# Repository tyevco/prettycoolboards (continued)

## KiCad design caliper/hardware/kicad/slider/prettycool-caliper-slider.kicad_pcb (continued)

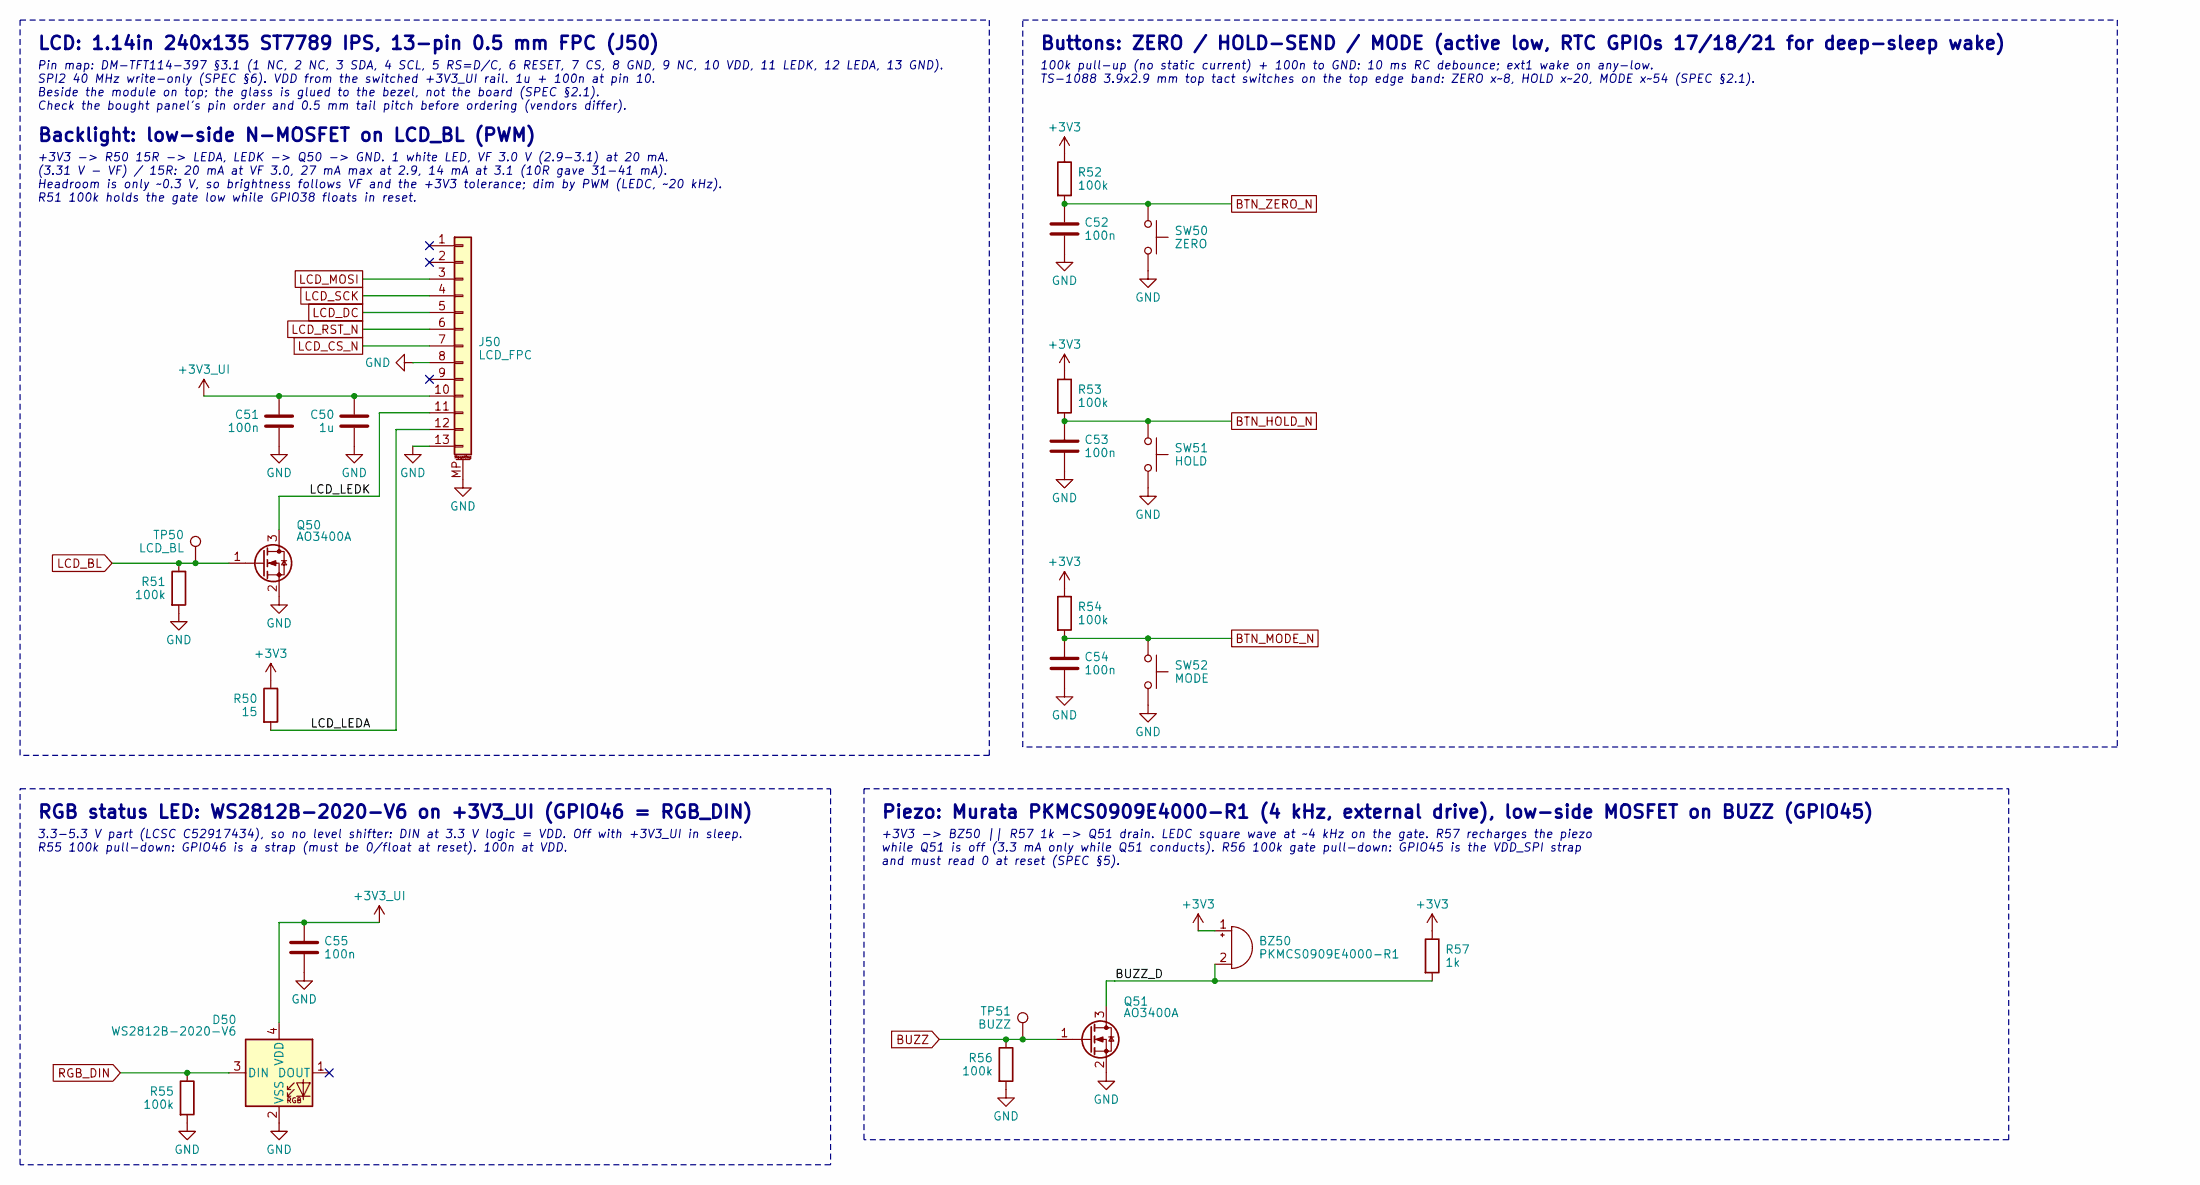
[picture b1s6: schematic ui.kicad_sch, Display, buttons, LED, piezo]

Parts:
BZ50: PKMCS0909E4000-R1; Buzzer_Murata_PKMCS0909E; MPN PKMCS0909E4000-R1; LCSC C910763
C50: 1u; C_0402_1005Metric; MPN CL05A105KA5NQNC; LCSC C52923
C51, C52, C53, C54, C55: 100n; C_0402_1005Metric; MPN CL05B104KO5NNNC; LCSC C1525
D50: WS2812B-2020-V6; LED_WS2812B-2020_PLCC4_2.0x2.0mm; MPN WS2812B-2020-V6; LCSC C52917434
J50: LCD_FPC; HDGC_0.5K-AX-13PWB_1x13-1MP_P0.50mm_Horizontal; MPN 0.5K-AX-13PWB; LCSC C2911931
Q50, Q51: AO3400A; SOT-23; MPN AO3400A; LCSC C20917
R50: 15; R_0603_1608Metric; MPN 0603WAF150JT5E; LCSC C22810
R51, R52, R53, R54, R55, R56: 100k; R_0402_1005Metric; MPN 0402WGF1003TCE; LCSC C25741
R57: 1k; R_0402_1005Metric; MPN 0402WGF1001TCE; LCSC C11702
SW50: ZERO; SW_SPST_TS-1088-xR020; MPN TS-1088-AR02016; LCSC C720477
SW51: HOLD; SW_SPST_TS-1088-xR020; MPN TS-1088-AR02016; LCSC C720477
SW52: MODE; SW_SPST_TS-1088-xR020; MPN TS-1088-AR02016; LCSC C720477
TP50: LCD_BL; TestPoint_Pad_D1.0mm
TP51: BUZZ; TestPoint_Pad_D1.0mm

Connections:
+3V3: BZ50.1 (+), R50.1, R52.1, R53.1, R54.1, R57.1; also elsewhere on the board
+3V3_UI: C50.1, C51.1, C55.1, D50.4 (VDD), J50.10; also elsewhere on the board
/Display, buttons, LED, piezo/BUZZ_D: BZ50.2 (-), Q51.3 (D), R57.2
/Display, buttons, LED, piezo/LCD_LEDA: J50.12, R50.2
/Display, buttons, LED, piezo/LCD_LEDK: J50.11, Q50.3 (D)
BTN_HOLD_N: C53.1, R53.2, SW51.1; also elsewhere on the board
BTN_MODE_N: C54.1, R54.2, SW52.1; also elsewhere on the board
BTN_ZERO_N: C52.1, R52.2, SW50.1; also elsewhere on the board
BUZZ: Q51.1 (G), R56.1, TP51.1; also elsewhere on the board
GND: C50.2, C51.2, C52.2, C53.2, C54.2, C55.2, D50.2 (VSS), J50.8, J50.13, J50.MP (MountPin), Q50.2 (S), Q51.2 (S), R51.2, R55.2, R56.2, SW50.2, SW51.2, SW52.2; also elsewhere on the board
LCD_BL: Q50.1 (G), R51.1, TP50.1; also elsewhere on the board
LCD_CS_N: J50.7; also elsewhere on the board
LCD_DC: J50.5; also elsewhere on the board
LCD_MOSI: J50.3; also elsewhere on the board
LCD_RST_N: J50.6; also elsewhere on the board
LCD_SCK: J50.4; also elsewhere on the board
RGB_DIN: D50.3 (DIN), R55.1; also elsewhere on the board

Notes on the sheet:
LCD: 1.14in 240x135 ST7789 IPS, 13-pin 0.5 mm FPC (J50)
Pin map: DM-TFT114-397 §3.1 (1 NC, 2 NC, 3 SDA, 4 SCL, 5 RS=D/C, 6 RESET, 7 CS, 8 GND, 9 NC, 10 VDD, 11 LEDK, 12 LEDA, 13 GND). SPI2 40 MHz write-only (SPEC §6). VDD from the switched +3V3_UI rail. 1u + 100n at pin 10. Beside the module on top; the glass is glued to the bezel, not the board (SPEC §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
Backlight: low-side N-MOSFET on LCD_BL (PWM)
+3V3 -> R50 15R -> LEDA, LEDK -> Q50 -> GND. 1 white LED, VF 3.0 V (2.9-3.1) at 20 mA. (3.31 V - VF) / 15R: 20 mA at VF 3.0, 27 mA max at 2.9, 14 mA at 3.1 (10R gave 31-41 mA). Headroom is only ~0.3 V, so brightness follows VF and the +3V3 tolerance; dim by PWM (LEDC, ~20 kHz). R51 100k holds the g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
Buttons: ZERO / HOLD-SEND / MODE (active low, RTC GPIOs 17/18/21 for deep-sleep wake)
100k pull-up (no static current) + 100n to GND: 10 ms RC debounce; ext1 wake on any-low. TS-1088 3.9x2.9 mm top tact switches on the top edge band: ZERO x~8, HOLD x~20, MODE x~54 (SPEC §2.1).
RGB status LED: WS2812B-2020-V6 on +3V3_UI (GPIO46 = RGB_DIN)
3.3-5.3 V part (LCSC C52917434), so no level shifter: DIN at 3.3 V logic = VDD. Off with +3V3_UI in sleep. R55 100k pull-down: GPIO46 is a strap (must be 0/float at reset). 100n at VDD.
Piezo: Murata PKMCS0909E4000-R1 (4 kHz, external drive), low-side MOSFET on BUZZ (GPIO45)
+3V3 -> BZ50 || R57 1k -> Q51 drain. LEDC square wave at ~4 kHz on the gate. R57 recharges the piezo while Q51 is off (3.3 mA only while Q51 conducts). R56 100k gate pull-down: GPIO45 is the VDD_SPI strap and must read 0 at reset (SPEC §5).

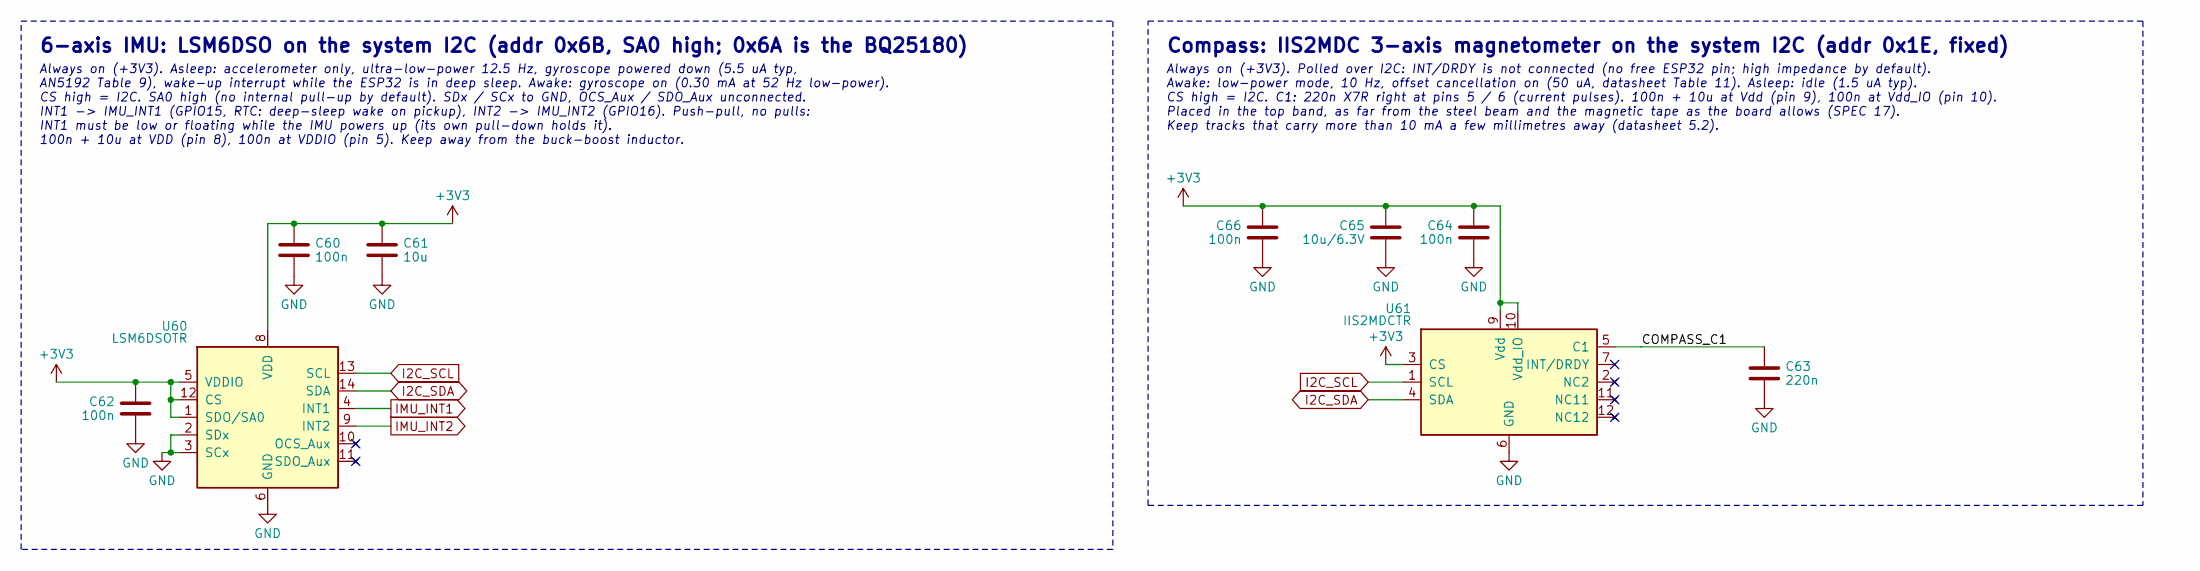
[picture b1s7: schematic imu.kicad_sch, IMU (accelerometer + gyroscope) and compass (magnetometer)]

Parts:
C60, C62, C64, C66: 100n; C_0402_1005Metric; MPN CL05B104KO5NNNC; LCSC C1525
C61: 10u; C_0603_1608Metric; MPN CL10A106KP8NNNC; LCSC C19702
C63: 220n; C_0402_1005Metric; MPN CL05B224KO5NNNC; LCSC C16772
C65: 10u/6.3V; C_0402_1005Metric; MPN CL05A106MQ5NUNC; LCSC C15525
U60: LSM6DSOTR; LGA-14_3x2.5mm_P0.5mm_LayoutBorder3x4y; MPN LSM6DSOTR; LCSC C2655100
U61: IIS2MDCTR; LGA-12_2x2mm_P0.5mm; MPN IIS2MDCTR; LCSC C2655002

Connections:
+3V3: C60.2, C61.2, C62.2, C64.2, C65.2, C66.2, U60.1 (SDO/SA0), U60.5 (VDDIO), U60.8 (VDD), U60.12 (CS), U61.3 (CS), U61.9 (Vdd), U61.10 (Vdd_IO); also elsewhere on the board
/IMU (accelerometer + gyroscope) and compass (magnetometer)/COMPASS_C1: C63.1, U61.5 (C1)
GND: C60.1, C61.1, C62.1, C63.2, C64.1, C65.1, C66.1, U60.2 (SDx), U60.3 (SCx), U60.6 (GND), U60.7 (GND), U61.6 (GND), U61.8 (GND); also elsewhere on the board
I2C_SCL: U60.13 (SCL), U61.1 (SCL); also elsewhere on the board
I2C_SDA: U60.14 (SDA), U61.4 (SDA); also elsewhere on the board
IMU_INT1: U60.4 (INT1); also elsewhere on the board
IMU_INT2: U60.9 (INT2); also elsewhere on the board

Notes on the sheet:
6-axis IMU: LSM6DSO on the system I2C (addr 0x6B, SA0 high; 0x6A is the BQ25180)
Always on (+3V3). Asleep: accelerometer only, ultra-low-power 12.5 Hz, gyroscope powered down (5.5 uA typ, AN5192 Table 9), wake-up interrupt while the ESP32 is in deep sleep. Awake: gyroscope on (0.30 mA at 52 Hz low-power). CS high = I2C. SA0 high (no internal pull-up by default). SDx / SCx to GN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
Compass: IIS2MDC 3-axis magnetometer on the system I2C (addr 0x1E, fixed)
Always on (+3V3). Polled over I2C: INT/DRDY is not connected (no free ESP32 pin; high impedance by default). Awake: low-power mode, 10 Hz, offset cancellation on (50 uA, datasheet Table 11). Asleep: idle (1.5 uA typ). CS high = I2C. C1: 220n X7R right at pins 5 / 6 (current pulses). 100n + 10u at V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

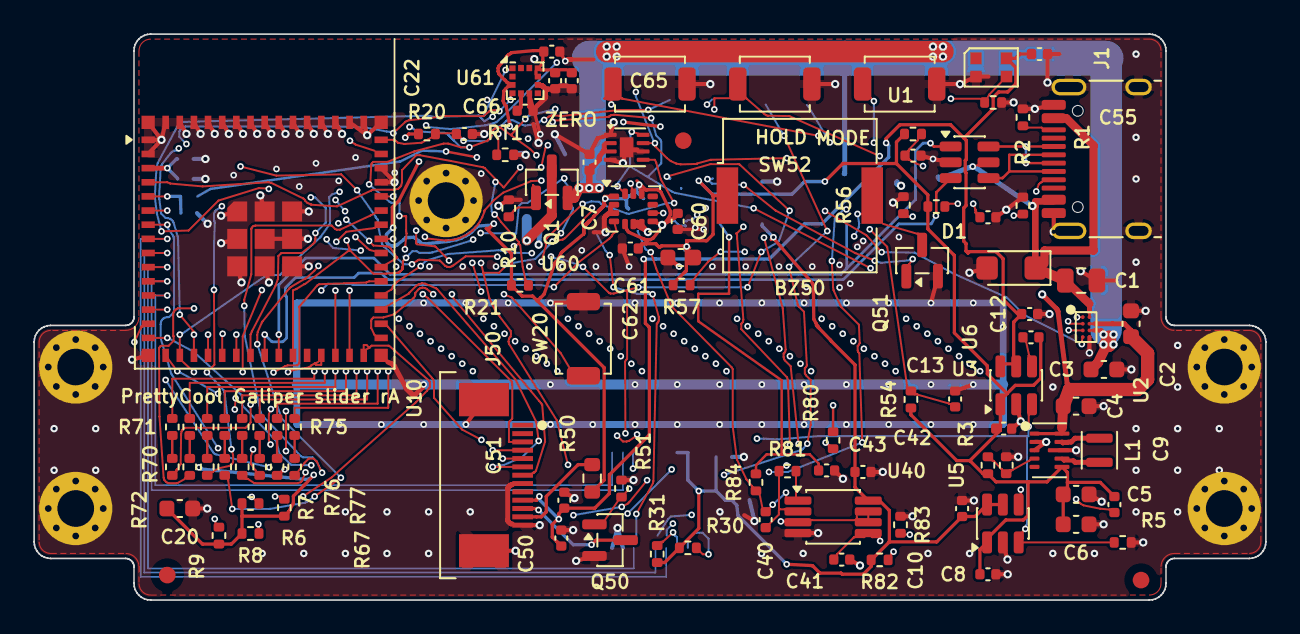
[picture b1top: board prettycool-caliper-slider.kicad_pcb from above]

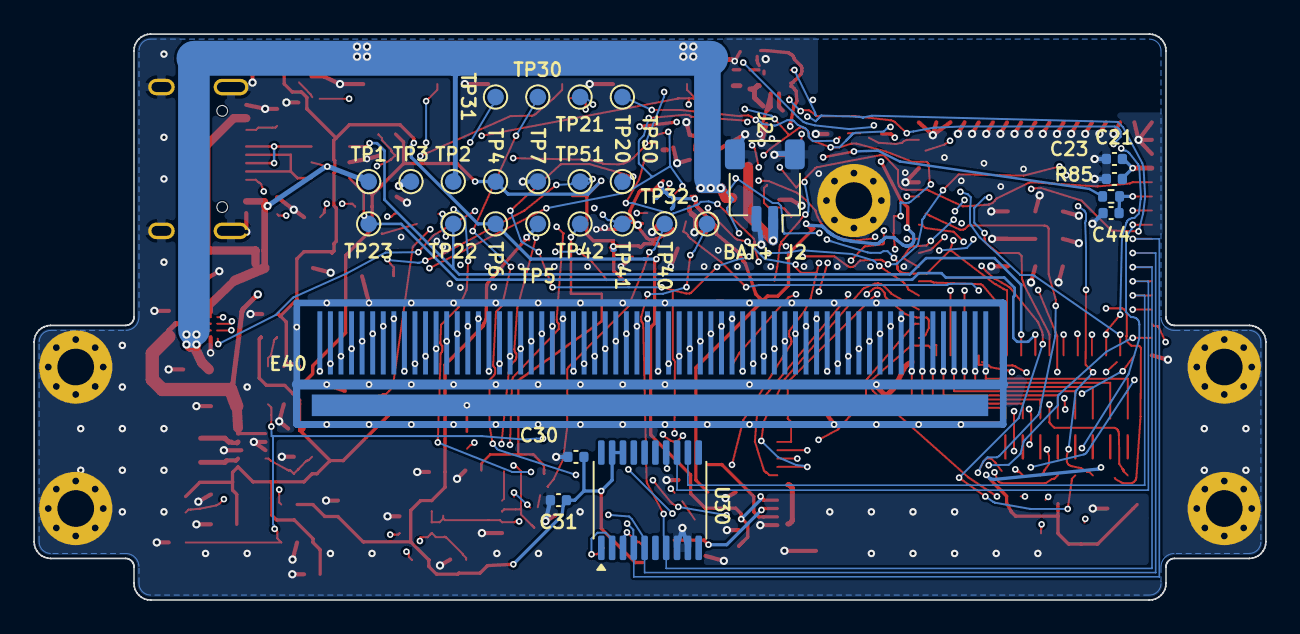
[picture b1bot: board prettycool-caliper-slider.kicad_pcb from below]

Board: 4 copper layers, 74.0 x 34.0 mm, 135 parts (28 on the bottom side), 82 nets.

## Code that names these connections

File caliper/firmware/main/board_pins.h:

/*
 * GENERATED by firmware/tools/gen_pins.py from caliper/hardware/design/nets.py. Do not edit.
 * nets.py REV A 2026-11-07
 */
#pragma once

#define BOARD_PINS_HASH "202d301f8ed3b0f1"
#define BOARD_REV "A"

/* GPIO number per net (ESP32-S3-MINI-1) */
#define PIN_BOOT_N      0  /* BOOT_N */
#define PIN_CAP_RX      1  /* CAP_RX */
#define PIN_FG_ALRT_N   2  /* FG_ALRT_N */
#define PIN_CHG_INT_N   3  /* CHG_INT_N */
#define PIN_MAG_A       4  /* MAG_A */
#define PIN_MAG_B       5  /* MAG_B */
#define PIN_MAG_IDX     6  /* MAG_IDX */
#define PIN_MAG_CLK     7  /* MAG_CLK */
#define PIN_MAG_DO      8  /* MAG_DO */
#define PIN_MAG_CSN     9  /* MAG_CSN */
#define PIN_MAG_INC_N  10  /* MAG_INC_N */
#define PIN_MAG_DEC_N  11  /* MAG_DEC_N */
#define PIN_SNS_PWR_EN 12  /* SNS_PWR_EN */
#define PIN_I2C_SDA    13  /* I2C_SDA */
#define PIN_I2C_SCL    14  /* I2C_SCL */
#define PIN_IMU_INT1   15  /* IMU_INT1 */
#define PIN_IMU_INT2   16  /* IMU_INT2 */
#define PIN_BTN_ZERO_N 17  /* BTN_ZERO_N */
#define PIN_BTN_HOLD_N 18  /* BTN_HOLD_N */
#define PIN_USB_DM     19  /* USB_DM */
#define PIN_USB_DP     20  /* USB_DP */
#define PIN_BTN_MODE_N 21  /* BTN_MODE_N */
#define PIN_LCD_SCK    33  /* LCD_SCK */
#define PIN_LCD_MOSI   34  /* LCD_MOSI */
#define PIN_LCD_CS_N   35  /* LCD_CS_N */
#define PIN_LCD_DC     36  /* LCD_DC */
#define PIN_LCD_RST_N  37  /* LCD_RST_N */
#define PIN_LCD_BL     38  /* LCD_BL */
#define PIN_CAP_TX0    39  /* CAP_TX0 */
#define PIN_CAP_TX1    40  /* CAP_TX1 */
#define PIN_CAP_TX2    41  /* CAP_TX2 */
#define PIN_CAP_TX3    42  /* CAP_TX3 */
#define PIN_CAP_TX6    43  /* CAP_TX6 */
#define PIN_CAP_TX7    44  /* CAP_TX7 */
#define PIN_BUZZ       45  /* BUZZ */
#define PIN_RGB_DIN    46  /* RGB_DIN */
#define PIN_CAP_TX4    47  /* CAP_TX4 */
#define PIN_CAP_TX5    48  /* CAP_TX5 */

/* 7-bit I2C addresses */
#define I2C_ADDR_BQ25180    0x6A
#define I2C_ADDR_IIS2MDC    0x1E
#define I2C_ADDR_LSM6DSO    0x6B
#define I2C_ADDR_MAX17048   0x36

/* CAP_TX0..7 in phase order, for the dedicated-GPIO bundle */
#define PIN_CAP_TX_LIST { PIN_CAP_TX0, PIN_CAP_TX1, PIN_CAP_TX2, PIN_CAP_TX3, PIN_CAP_TX4, PIN_CAP_TX5, PIN_CAP_TX6, PIN_CAP_TX7 }

/* every GPIO above, for checks (test/host/test_pin_plan.c: each one is in the pin plan) */
#define BOARD_PINS_COUNT 38
#define BOARD_PINS_ALL { \
    PIN_BOOT_N, PIN_CAP_RX, PIN_FG_ALRT_N, PIN_CHG_INT_N, PIN_MAG_A, PIN_MAG_B, \
    PIN_MAG_IDX, PIN_MAG_CLK, PIN_MAG_DO, PIN_MAG_CSN, PIN_MAG_INC_N, PIN_MAG_DEC_N, \
    PIN_SNS_PWR_EN, PIN_I2C_SDA, PIN_I2C_SCL, PIN_IMU_INT1, PIN_IMU_INT2, PIN_BTN_ZERO_N, \
    PIN_BTN_HOLD_N, PIN_USB_DM, PIN_USB_DP, PIN_BTN_MODE_N, PIN_LCD_SCK, PIN_LCD_MOSI, \
    PIN_LCD_CS_N, PIN_LCD_DC, PIN_LCD_RST_N, PIN_LCD_BL, PIN_CAP_TX0, PIN_CAP_TX1, \
    PIN_CAP_TX2, PIN_CAP_TX3, PIN_CAP_TX6, PIN_CAP_TX7, PIN_BUZZ, PIN_RGB_DIN, \
    PIN_CAP_TX4, PIN_CAP_TX5 \
}

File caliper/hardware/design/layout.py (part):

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        "D50": (51.5, 32.0, 0.0, "F"),
        # 2026-11-09 slim housing (owner decision): J2 on the BOTTOM, hanging into the battery pocket's J2 bay (board
        # x 21.5..27.6, y 22.4..35.1), mating face toward +y (the top edge), signal pads toward -y (pad row y 22.9,
        # pin 1 VBAT_RAW at x 23.6). Body x 22.1..26.1, y 23.2..27.5, 2.95 below the board; the mated plug x 21.9..26.3,
        # y 27.5..32.1. Was (24.5, 30.6) rot 180 on top, mouth over the top edge (plug relief past y 34 in the housing).
        # >= 6.3 mm in plan from the antenna area, >= 0.9 mm from H1's boss
        "J2": (24.1, 24.9, 0.0, "B"),
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        # (2.0, 25.95): C21 100n above, C23 10u below, +3V3 pad (1) toward the via. 0402, 0.5 mm tall, in the upper
        # band where the housing floor is 0.75 mm below the board (SPEC §2.1); clear of the antenna rule area (y >= 29.2)
        "C21": (3.1, 26.5, 0.0, "B"), "C23": (3.1, 25.3, 0.0, "B"),
        # CAP_RX anti-alias RC (3.9k / 100p) at the ADC pin (review 2026-11-08: it sat at U40, 40 mm of track from
        # GPIO1): bottom, under the module, below C23, beside GPIO1's escape via (2.0, 24.25); R85 pad 2 (CAP_RX)
        # and C44 pad 1 (CAP_RX) face the via. 0.2 mm from every other net (the Analog class), 0.5 mm tall
        "R85": (3.3, 24.25, 180.0, "B"), "C44": (3.3, 23.25, 0.0, "B"),
        # FID3 (SPEC 60.5, 32.8) would sit inside J1's courtyard (it reaches y 31.9 over x 54-63): top middle instead
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        if ref in fps:
            d = local_dir_board(fps[ref], lx, ly)
            assert abs(d[0] - want[0]) < 0.05 and abs(d[1] - want[1]) < 0.05, f"{ref} opens toward {d}, want {want}"
    if "J2" in fps:      # bottom side; a bottom part is mirrored, so pin 1 (VBAT_RAW) is the -x one of the pair
        assert fps["J2"].IsFlipped(), "J2 must be on the bottom (SPEC §2.1)"
        p1, p2 = pad_xy(fps["J2"], "1"), pad_xy(fps["J2"], "2")
        assert abs(p1[1] - 22.9) < 0.01 and p1[0] < p2[0], f"J2 pins at {p1} / {p2}, want the row at y 22.9, pin 1 -x"
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                   # the module peaks at ~0.36 A) in a class the grid router may rip up and re-route
                   rail_nets=("+3V3",),
                   light_power=("+3V3_SNS", "+3V3_UI", "LCD_LEDA", "LCD_LEDK"),
                   # CAP_RX (GPIO1, ADC) and the long run to its filter's first stage (review 2026-11-08)
                   analog_nets=("CAP_RX", "CAP_LP1"),
                   gnd_fanout=True, route=True, edge=0.25, stitch_pitch=2.5, stackup="slider",
                   # USBLC6-2SC6: I/O1 (pins 1/6) and I/O2 (3/4) are one conductor inside the part. As jumper pad
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
def preroute_vbat_raw(bb):
    """J2 pin 1 -> Q1 drain, 0.60 mm (the pads' width) instead of the 0.30 mm Power class. J2 is on the bottom since
    2026-11-09 with Q1 above it on top: B.Cu from pin 1 (23.6, 22.9) straight down (away from CAP_LP1's In2 stretch,
    which passes 1.1 mm above the pad centre: the stub stays out of its B.Cu shield band) to a via at (23.6, 21.6),
    then F.Cu at 45 degrees and up x 25.1 between Q1's gate and source pads into the drain pad."""
    fps = bb.footprints
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    net = bb.net("VBAT_RAW")
    j2, q1d = pad_xy(fps["J2"], net="VBAT_RAW"), pad_xy(fps["Q1"], net="VBAT_RAW")
    v = VBAT_RAW_VIA
    assert abs(j2[0] - v[0]) < 0.01, f"J2 pin 1 at {j2}: the VBAT_RAW via column assumes x {v[0]}"
    add_path(bb.board, [j2, v], pcbnew.B_Cu, net, 0.6)
    add_vias(bb.board, [v], net)
    add_path(bb.board, [v, (q1d[0], v[1] + (q1d[0] - v[0])), q1d], pcbnew.F_Cu, net, 0.6)
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        return
    net = _elnet(bb, "CAP_RX")
    r85, c44 = pad_xy(fps["R85"], net="CAP_RX"), pad_xy(fps["C44"], net="CAP_RX")
    gpio1 = pad_xy(fps["U10"], net="CAP_RX")
    via = (gpio1[0] + 1.15, gpio1[1])                      # escape_module()'s via
    assert r85[0] < pad_xy(fps["R85"], net="CAP_LP1")[0], "R85's CAP_RX pad must face the escape via (west)"
    add_path(bb.board, [via, r85, c44], pcbnew.B_Cu, net, 0.2)
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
